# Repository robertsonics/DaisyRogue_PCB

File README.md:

# DaisyRogue_PCB
Daisy Rogue PCB KiCad Project

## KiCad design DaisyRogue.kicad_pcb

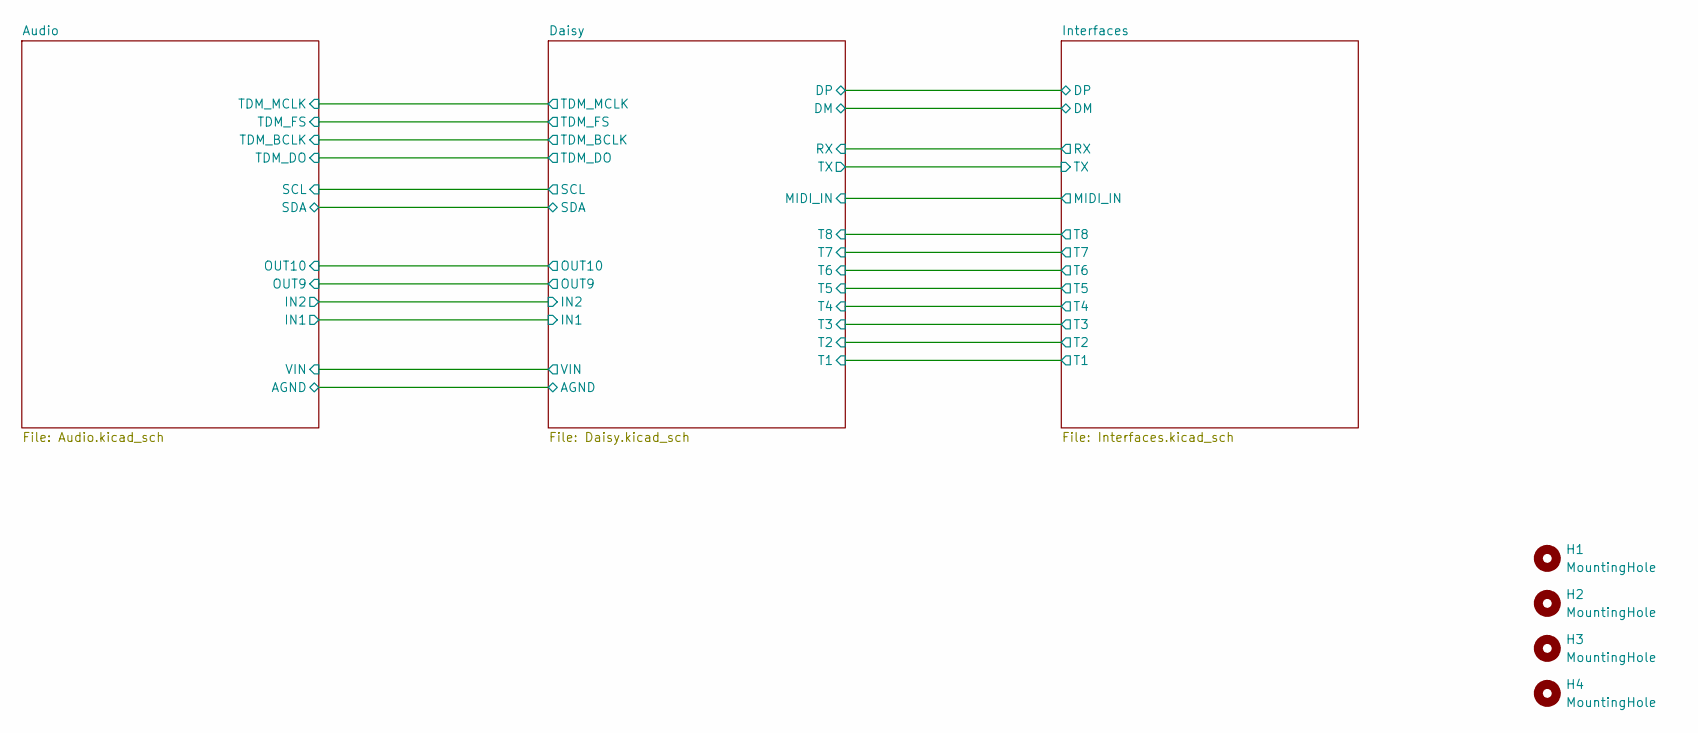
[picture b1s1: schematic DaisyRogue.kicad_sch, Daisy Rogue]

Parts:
H1, H2, H3, H4: MountingHole; MountingHole_2.7mm_Pad_TopBottom

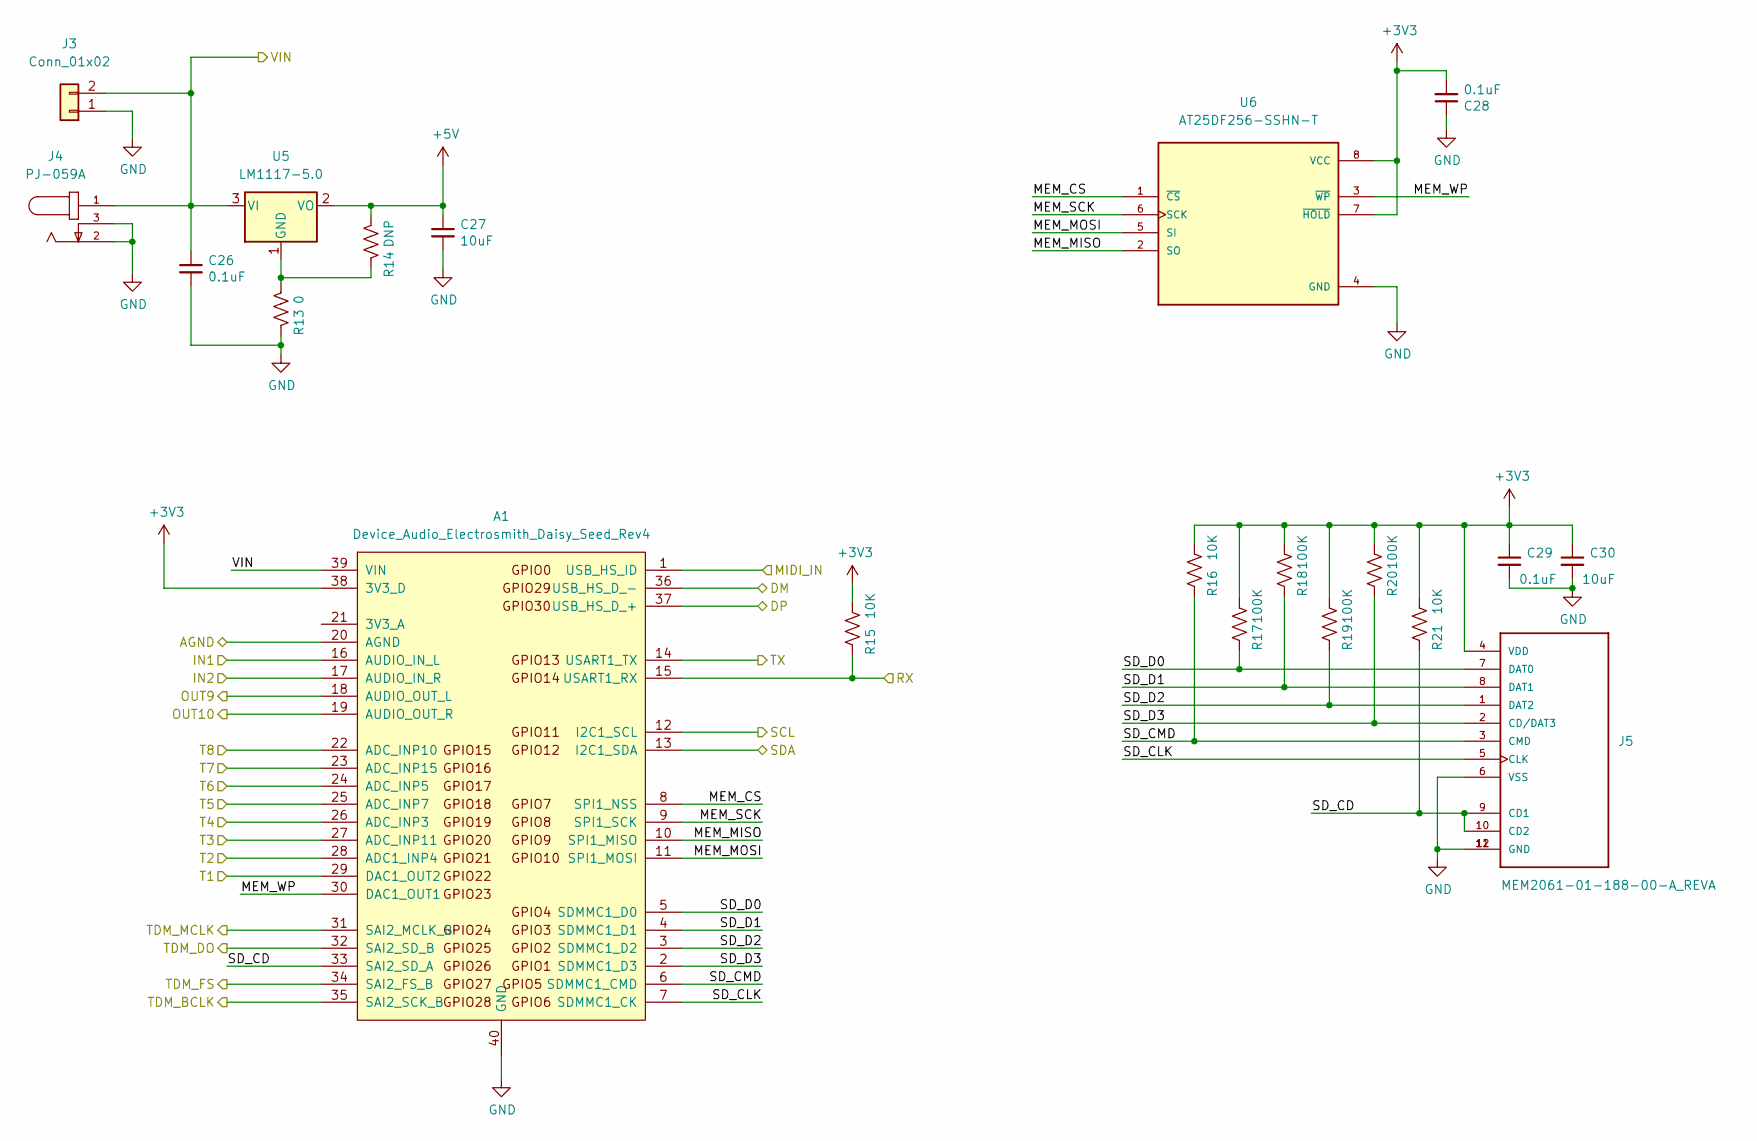
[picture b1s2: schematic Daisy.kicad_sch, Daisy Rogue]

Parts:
A1: Device_Audio_Electrosmith_Daisy_Seed_Rev4; Device_Audio_Electrosmith_Daisy_Seed
C26, C28, C29: 0.1uF; C_0603_1608Metric
C27, C30: 10uF; C_0805_2012Metric
J3: Conn_01x02; PinHeader_1x02_P2.54mm_Vertical
J4: PJ-059A; CUI_PJ-059A; PARTREV 1.02
J5: MEM2061-01-188-00-A_REVA
R13: 0; R_0603_1608Metric
R14: DNP; R_0603_1608Metric
R15, R16, R21: 10K; R_0603_1608Metric
R17, R18, R19, R20: 100K; R_0603_1608Metric
U5: LM1117-5.0; SOT-223-3_TabPin2
U6: AT25DF256-SSHN-T; SOIC127P599X175-8N; PARTREV 5/2017

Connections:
+3V3: A1.38 (3V3_D), C28.2, C29.1, C30.1, J5.4 (VDD), R15.1, R16.1, R17.1, R18.1, R19.1, R20.1, R21.1, U6.7 (~HOLD), U6.8 (VCC); also elsewhere on the board
+5V: C27.1, R14.2, U5.2 (VO); also elsewhere on the board
/Audio/IN1: A1.16 (AUDIO_IN_L); also elsewhere on the board
/Audio/IN2: A1.17 (AUDIO_IN_R); also elsewhere on the board
/Audio/OUT9: A1.18 (AUDIO_OUT_L); also elsewhere on the board
/Audio/OUT10: A1.19 (AUDIO_OUT_R); also elsewhere on the board
/Audio/SCL: A1.12 (I2C1_SCL); also elsewhere on the board
/Audio/SDA: A1.13 (I2C1_SDA); also elsewhere on the board
/Audio/TDM_BCLK: A1.35 (SAI2_SCK_B); also elsewhere on the board
/Audio/TDM_DO: A1.32 (SAI2_SD_B); also elsewhere on the board
/Audio/TDM_FS: A1.34 (SAI2_FS_B); also elsewhere on the board
/Audio/TDM_MCLK: A1.31 (SAI2_MCLK_B); also elsewhere on the board
/Daisy/DM: A1.36 (USB_HS_D_-); also elsewhere on the board
/Daisy/DP: A1.37 (USB_HS_D_+); also elsewhere on the board
/Daisy/MEM_CS: A1.8 (SPI1_NSS), U6.1 (~CS)
/Daisy/MEM_MISO: A1.10 (SPI1_MISO), U6.2 (SO)
/Daisy/MEM_MOSI: A1.11 (SPI1_MOSI), U6.5 (SI)
/Daisy/MEM_SCK: A1.9 (SPI1_SCK), U6.6 (SCK)
/Daisy/MEM_WP: A1.30 (DAC1_OUT1), U6.3 (~WP)
/Daisy/MIDI_IN: A1.1 (USB_HS_ID); also elsewhere on the board
/Daisy/RX: A1.15 (USART1_RX), R15.2; also elsewhere on the board
/Daisy/SD_CD: A1.33 (SAI2_SD_A), J5.9 (CD1), J5.10 (CD2), R21.2
/Daisy/SD_CLK: A1.7 (SDMMC1_CK), J5.5 (CLK)
/Daisy/SD_CMD: A1.6 (SDMMC1_CMD), J5.3 (CMD), R16.2
/Daisy/SD_D0: A1.5 (SDMMC1_D0), J5.7 (DAT0), R17.2
/Daisy/SD_D1: A1.4 (SDMMC1_D1), J5.8 (DAT1), R18.2
/Daisy/SD_D2: A1.3 (SDMMC1_D2), J5.1 (DAT2), R19.2
/Daisy/SD_D3: A1.2 (SDMMC1_D3), J5.2 (CD/DAT3), R20.2
/Daisy/T1: A1.29 (DAC1_OUT2); also elsewhere on the board
/Daisy/T2: A1.28 (ADC1_INP4); also elsewhere on the board
/Daisy/T3: A1.27 (ADC_INP11); also elsewhere on the board
/Daisy/T4: A1.26 (ADC_INP3); also elsewhere on the board
/Daisy/T5: A1.25 (ADC_INP7); also elsewhere on the board
/Daisy/T6: A1.24 (ADC_INP5); also elsewhere on the board
/Daisy/T7: A1.23 (ADC_INP15); also elsewhere on the board
/Daisy/T8: A1.22 (ADC_INP10); also elsewhere on the board
/Daisy/TX: A1.14 (USART1_TX); also elsewhere on the board
/Daisy/VIN: A1.39 (VIN), C26.1, J3.2, J4.1, U5.3 (VI); also elsewhere on the board
GND: A1.40 (GND), C26.2, C27.2, C28.1, C29.2, C30.2, J3.1, J4.2, J4.3, J5.6 (VSS), J5.11 (GND), J5.12 (GND), R13.2, U6.4 (GND); also elsewhere on the board
GNDA: A1.20 (AGND); also elsewhere on the board
unnamed: R13.1, R14.1, U5.1 (GND)

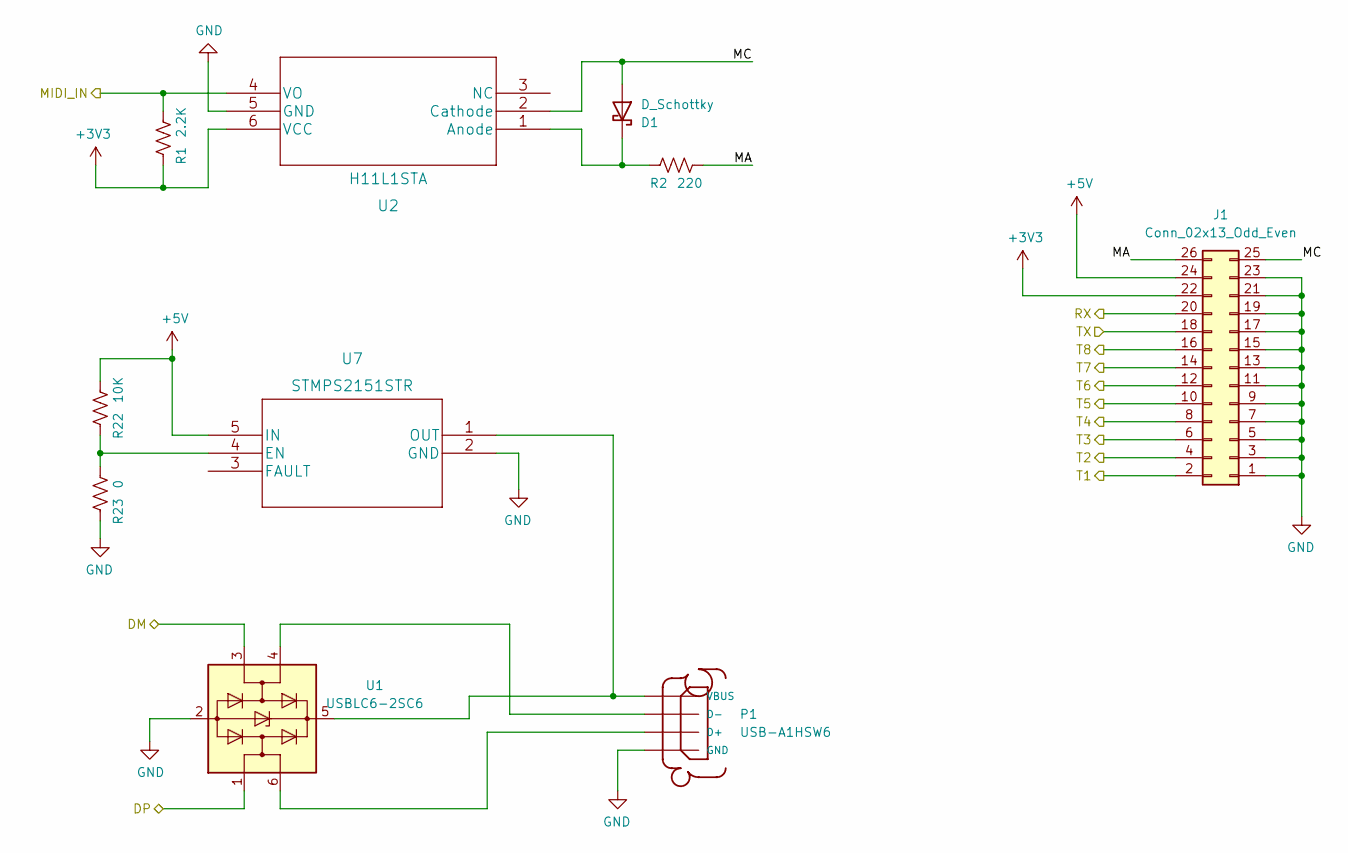
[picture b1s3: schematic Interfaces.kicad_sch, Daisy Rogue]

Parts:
D1: D_Schottky; D_SOD-323
J1: Conn_02x13_Odd_Even; PinHeader_2x13_P2.54mm_Vertical
P1: USB-A1HSW6; OST_USB-A1HSW6
R1: 2.2K; R_0603_1608Metric
R2: 220; R_0603_1608Metric
R22: 10K; R_0603_1608Metric
R23: 0; R_0603_1608Metric
U1: USBLC6-2SC6; SOT-23-6
U2: H11L1STA
U7: STMPS2151STR; SOT-23-5

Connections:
+3V3: J1.22, R1.2, U2.6 (VCC); also elsewhere on the board
+5V: J1.24, R22.1, U7.5 (IN); also elsewhere on the board
/Daisy/DM: U1.3 (I/O2); also elsewhere on the board
/Daisy/DP: U1.1 (I/O1); also elsewhere on the board
/Daisy/MIDI_IN: R1.1, U2.4 (VO); also elsewhere on the board
/Daisy/RX: J1.20; also elsewhere on the board
/Daisy/T1: J1.2; also elsewhere on the board
/Daisy/T2: J1.4; also elsewhere on the board
/Daisy/T3: J1.6; also elsewhere on the board
/Daisy/T4: J1.8; also elsewhere on the board
/Daisy/T5: J1.10; also elsewhere on the board
/Daisy/T6: J1.12; also elsewhere on the board
/Daisy/T7: J1.14; also elsewhere on the board
/Daisy/T8: J1.16; also elsewhere on the board
/Daisy/TX: J1.18; also elsewhere on the board
/Interfaces/MA: J1.26, R2.1
/Interfaces/MC: D1.2 (A), J1.25, U2.2 (Cathode)
GND: J1.1, J1.3, J1.5, J1.7, J1.9, J1.11, J1.13, J1.15, J1.17, J1.19, J1.21, J1.23, P1.4 (GND), R23.2, U1.2 (GND), U2.5 (GND), U7.2 (GND); also elsewhere on the board
unnamed: D1.1 (K), R2.2, U2.1 (Anode)
unnamed: P1.1 (VBUS), U1.5 (VBUS), U7.1 (OUT)
unnamed: P1.2 (D-), U1.4 (I/O2)
unnamed: P1.3 (D+), U1.6 (I/O1)
unnamed: R22.2, R23.1, U7.4 (EN)

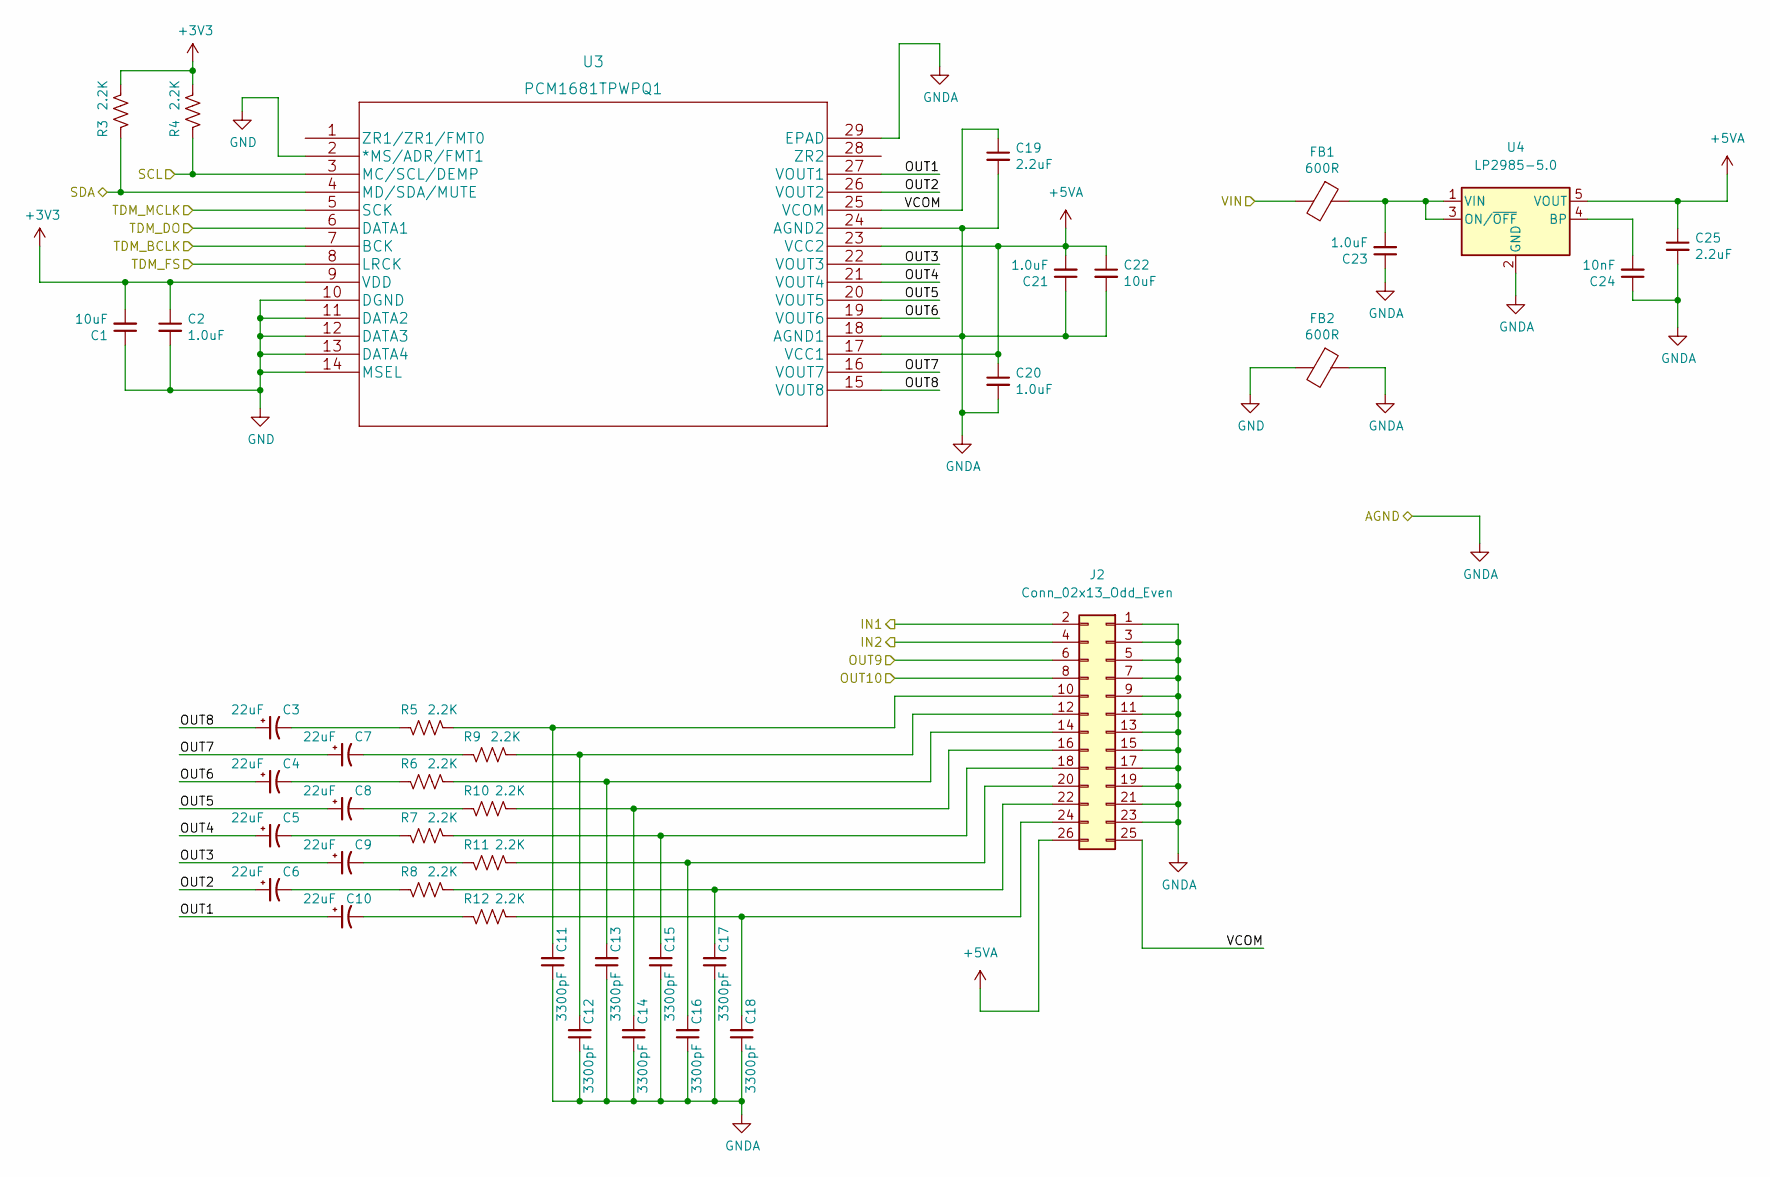
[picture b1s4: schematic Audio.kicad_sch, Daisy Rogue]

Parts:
C1, C22: 10uF; C_0805_2012Metric
C2, C20, C21, C23: 1.0uF; C_0603_1608Metric
C3, C4, C5, C6, C7, C8, C9, C10: 22uF; C_1206_3216Metric
C11, C12, C13, C14, C15, C16, C17, C18: 3300pF; C_0603_1608Metric
C19, C25: 2.2uF; C_0603_1608Metric
C24: 10nF; C_0603_1608Metric
FB1, FB2: 600R; L_0603_1608Metric
J2: Conn_02x13_Odd_Even; PinHeader_2x13_P2.54mm_Vertical
R3, R4, R5, R6, R7, R8, R9, R10, R11, R12: 2.2K; R_0603_1608Metric
U3: PCM1681TPWPQ1
U4: LP2985-5.0; SOT-23-5

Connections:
+3V3: C1.2, C2.1, R3.1, R4.1, U3.9 (VDD); also elsewhere on the board
+5VA: C20.1, C21.2, C22.1, C25.1, J2.26, U3.17 (VCC1), U3.23 (VCC2), U4.5 (VOUT)
/Audio/IN1: J2.2; also elsewhere on the board
/Audio/IN2: J2.4; also elsewhere on the board
/Audio/OUT1: C10.1, U3.27 (VOUT1)
/Audio/OUT2: C6.1, U3.26 (VOUT2)
/Audio/OUT3: C9.1, U3.22 (VOUT3)
/Audio/OUT4: C5.1, U3.21 (VOUT4)
/Audio/OUT5: C8.1, U3.20 (VOUT5)
/Audio/OUT6: C4.1, U3.19 (VOUT6)
/Audio/OUT7: C7.1, U3.16 (VOUT7)
/Audio/OUT8: C3.1, U3.15 (VOUT8)
/Audio/OUT9: J2.6; also elsewhere on the board
/Audio/OUT10: J2.8; also elsewhere on the board
/Audio/SCL: R4.2, U3.3 (MC/SCL/DEMP); also elsewhere on the board
/Audio/SDA: R3.2, U3.4 (MD/SDA/MUTE); also elsewhere on the board
/Audio/TDM_BCLK: U3.7 (BCK); also elsewhere on the board
/Audio/TDM_DO: U3.6 (DATA1); also elsewhere on the board
/Audio/TDM_FS: U3.8 (LRCK); also elsewhere on the board
/Audio/TDM_MCLK: U3.5 (SCK); also elsewhere on the board
/Audio/VCOM: C19.1, J2.25, U3.25 (VCOM)
/Daisy/VIN: FB1.2; also elsewhere on the board
GND: C1.1, C2.2, FB2.2, U3.2 (*MS/ADR/FMT1), U3.10 (DGND), U3.11 (DATA2), U3.12 (DATA3), U3.13 (DATA4), U3.14 (MSEL); also elsewhere on the board
GNDA: C11.1, C12.1, C13.1, C14.1, C15.1, C16.1, C17.1, C18.1, C19.2, C20.2, C21.1, C22.2, C23.1, C24.1, C25.2, FB2.1, J2.1, J2.3, J2.5, J2.7, J2.9, J2.11, J2.13, J2.15, J2.17, J2.19, J2.21, J2.23, U3.18 (AGND1), U3.24 (AGND2), U3.29 (EPAD), U4.2 (GND); also elsewhere on the board
unnamed: C3.2, R5.2
unnamed: C4.2, R6.2
unnamed: C5.2, R7.2
unnamed: C6.2, R8.2
unnamed: C7.2, R9.2
unnamed: C8.2, R10.2
unnamed: C9.2, R11.2
unnamed: C10.2, R12.2
unnamed: C11.2, J2.10, R5.1
unnamed: C12.2, J2.12, R9.1
unnamed: C13.2, J2.14, R6.1
unnamed: C14.2, J2.16, R10.1
unnamed: C15.2, J2.18, R7.1
unnamed: C16.2, J2.20, R11.1
unnamed: C17.2, J2.22, R8.1
unnamed: C18.2, J2.24, R12.1
unnamed: C23.2, FB1.1, U4.1 (VIN), U4.3 (ON/~OFF)
unnamed: C24.2, U4.4 (BP)

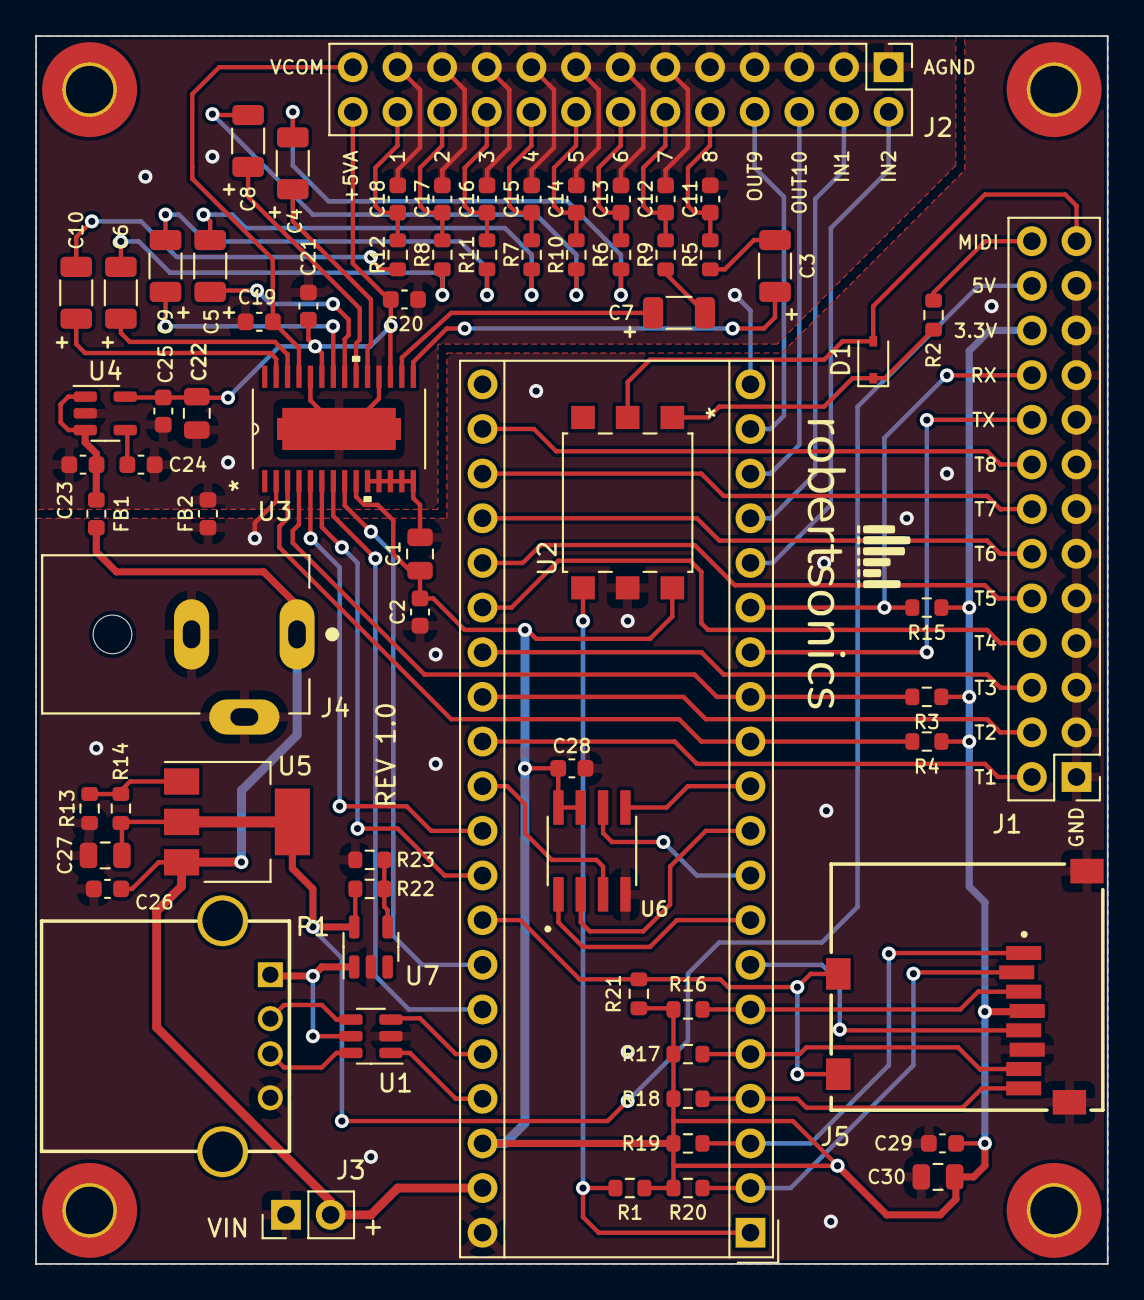
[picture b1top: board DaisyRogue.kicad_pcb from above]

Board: 2 copper layers, 61.0 x 69.8 mm, 74 parts (0 on the bottom side), 76 nets.

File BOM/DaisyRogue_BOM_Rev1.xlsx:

Daisy Rogue Audio Board Rev1 |  | Updated 10/31/2022
Item # | Reference | Qty | Do Not Popluate | Manufacturer Part # | Manufacturer | Value | Vendor | Vendor Part # | Price | Extended Price | DNP | Footprint | Substitution Notes
1 | A1, | 1 | DNP | Daisy Seed | ElectroSmith |  | ElectroSmith | Daisy Seed |  |  |  | DAISY SEED
 |  | 2 | DNP | PPTC201LFBN-RC | Sullins |  | Digikey | S7018-ND | 0.93 |  | 1.86 | 1x20, 0.1" Female header
2 | C1, C22, C27, C30, | 4 |  | CC0805KRX5R6BB106 | Yageo | 10uF | Digikey | 311-3424-1-ND | 0.22 | 0.88 |  | C_0805_2012Metric | >= 10V, X7R
3 | C2, C20, C21, C23, | 4 |  | C0603C105K4PAC7867 | Kemet | 1.0uF | Digikey | 399-C0603C105K4PAC7867CT-ND | 0.05 | 0.2 |  | C_0603_1608Metric | CL10B105KA8NNNL Okay
4 | C11, C12, C13, C14, C15, C16, C17, C18, | 8 |  | C1608C0G1H332J080AA | TDK | 3300pF | Digikey | 445-1599-1-N | 0.14000000000000001 | 1.1200000000000001 |  | C_0603_1608Metric | >=10V, <= 5%, COG/NP0
5 | C3, C4, C5, C6, C7, C8, C9, C10, | 8 |  | TL8W9226M010C | Vishay | 22uF | Digikey | 718-1917-1-ND | 0.34 | 2.72 |  | C_1206_3216Metric | >=10V, Tantalum
6 | C19, C25, | 2 |  | C0603C225K4PAC7867 | Kemet | 2.2uF | Digikey | 399-C0603C225K4PAC7867CT-ND | 0.05 | 0.1 |  | C_0603_1608Metric | >=10V, X7R
7 | C24, | 1 |  | C0603C103M5RAC7411 | Kemet | 10nF | Digikey | 399-C0603C103M5RAC7411CT-ND | 0.02 | 0.02 |  | C_0603_1608Metric | >=10V, X7R
8 | C26, C28, C29, | 3 |  | C0603C104K9PAC7867 | Kemet | 0.1uF | Digikey | 399-17575-1-ND | 0.08 | 0.24 |  | C_0603_1608Metric | >=10V
9 | D1, | 1 |  | NSR1020MW2T3G | Onsemi | D_Schottky | Digikey | NSR1020MW2T3GOSCT-ND | 0.33 | 0.33 |  | SOD-323
10 | FB1, FB2, | 2 |  | MI0603J601R-10 | Laird | 600R | Digikey | 240-2371-1-ND | 0.11 | 0.22 |  | L_0603_1608Metric | FBH160808T-601Y-S Okay
11 | R2, | 1 |  | RMCF0603JT220R | Stackpole | 220 | Digikey | RMCF0603JT220RCT-ND | 0.02 | 0.02 |  | R_0603_1608Metric | 1% - 5%
12 | R1, R3, R4, R5, R6, R7, R8, R9, R10, R11, R12 | 11 |  | RMCF0603JT2K20 | Stackpole | 2.2K | Digikey | RMCF0603JT2K20CT-ND | 0.01 | 0.11 |  | R_0603_1608Metric | 0.01
13 | R13, | 1 |  | RMCF0603ZT0R00 | Stackpole | 0 | Digikey | RMCF0603ZT0R00CT-ND | 0.01 | 0.01 |  | R_0603_1608Metric | 1% - 5%
14 | R14, | 1 | DNP |  |  |  |  |  |  |  |  | R_0603_1608Metric | 0.01
15 | R15, R16, R21, R22, | 4 |  | RMCF0603JT10K0 | Stackpole | 10K | Digikey | RMCF0603JT10K0CT-ND | 0.02 | 0.08 |  | R_0603_1608Metric | 1% - 5%
16 | R17, R18, R19, R20, | 4 |  | RMCF0603JT100K | Stackpole | 100K | Digikey | RMCF0603JT100KCT-ND | 0.02 | 0.08 |  | R_0603_1608Metric | 1% - 5%
17 | R23, | 1 | DNP |  |  |  |  |  |  |  |  | R_0603_1608Metric | 1% - 5%
18 | U1, | 1 |  | USBLC6-2SC6 | STMicro |  | Digikey | 497-5235-1-ND | 0.54 | 0.54 |  | SOT-23-6
19 | U2, | 1 |  | H11L1STA | Everlight |  | Digikey | 1080-1201-1-ND | 0.5 | 0.5 |  | 6-SMD
20 | U3, | 1 |  | PCM1681TPWPQ1 | TI |  | Arrow | PCM1681TPWPQ1 | 3.51 | 3.51 |  | 28-HTSSOP
21 | U4, | 1 |  | LP2985AIM5X-5.0/NOPB | TI |  | Digikey | LP2985AIM5X-5.0/NOPBCT-ND | 0.8 | 0.8 |  | SOT-23-5
22 | U5, | 1 |  | LD1117S50CTR | STMicro |  | Digikey | 497-1243-1-ND | 0.53 | 0.53 |  | SOT-223
23 | U6, | 1 |  | AT25DF256-SSHN-T | Adesto |  | Digikey | 1265-1111-1-ND | 0.5 | 0.5 |  | 8-SOIC
24 | U7, | 1 |  | STMPS2151STR | STMicro |  | Mouser | 511-STMPS2151STR | 1 | 1 |  | SOT-23-5 | STMPS2141STR Okay with resistor change
25 | P1, | 1 | DNP | USB-A1HSW6 | On Shore |  | Digikey | ED2989-ND | 0.36 |  | 0.36 | GCT_USB4105_REVA
26 | J1, J2, | 2 | DNP | PRPC013DAAN-RC | Sullins |  | Digikey | S2011EC-13-ND | 0.46 |  | 0.92 | 2x13, 0.1" Header
27 | J3 | 1 | DNP |  |  |  |  |  |  |  |  | 1x2, 0.1" Header
28 | J4, | 1 | DNP | PJ-059A | CUI |  | Digikey | CP-059A-ND | 0.68 |  | 0.68 | CUI_PJ-059A
29 | J5, | 1 |  | MEM2061-01-188-00-A | GCT |  | Digikey | 2073-MEM2061-01-188-00-ACT-ND | 1 | 1 |  | MEM2061-01-188-00-A_REVA
 |  |  |  |  |  |  |  |  |  |  | 3.8200000000000003

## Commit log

2023-03-04 First production version initial repo upload.

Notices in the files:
parts and their libraries:
Copyright 2021 Accelerated Designs. All rights reserved.
